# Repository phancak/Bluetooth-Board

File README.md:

# STM32WB55CGU6 Bluetooth Expansion Board  

## Overview  
This project showcases a **high-performance Bluetooth expansion board** based on the **STM32WB55CGU6 module**, a dual-core **Cortex-M4/M0+** MCU with integrated **Bluetooth 5.2** support. Designed for seamless connectivity and modular integration, the board enables **wireless communication** for a wide range of embedded applications.  

This expansion board provides **I2C, USART, and SPI interfaces**, making it a versatile platform for **IoT, industrial control, and smart embedded systems**.  

## Features  
✅ **STM32WB55CGU6 MCU** – Dual-core architecture with BLE 5.2 support  
✅ **Multiple Communication Interfaces** – I2C, USART, SPI for flexible connectivity  
✅ **Ultra-Low Power Operation** – Optimized for battery-powered applications  
✅ **Compact and Modular Design** – Easy integration with host MCUs  
✅ **Secure BLE Communication** – Integrated AES-256 encryption for data protection  

## Applications  
- **IoT & Smart Devices** – Wireless sensors, home automation, asset tracking  
- **Industrial Automation** – Wireless monitoring, factory communication systems  
- **Embedded Development** – Prototyping for BLE-enabled applications  

## Getting Started  
### Hardware Requirements  
- STM32WB55CGU6 Bluetooth Expansion Board  
- Host MCU (STM32, ESP32, Raspberry Pi, etc.)  
- Power Supply (3.3V)  
- USB-to-Serial Debugging Tools  

### Software Requirements  
- **STM32CubeIDE** – Firmware development  
- **STM32CubeWB** – BLE stack and middleware  
- **ST-Link or J-Link** – Debugging and flashing tools  

## Setup & Usage  
1. **Power the Board** – Connect 3.3V power via USB or external source.  
2. **Establish Communication** – Interface using I2C, USART, or SPI.  
3. **Flash Firmware** – Use STM32CubeIDE for code deployment.  
4. **Test Bluetooth Functionality** – Verify BLE communication via a mobile app or BLE-enabled host.  

## Repository Structure  
/Hardware - PCB schematics and design files
/Schematic - Circuit diagrams (PDF, KiCad, Altium, etc.)
/PCB - Board layout files (Gerber, BOM, assembly files)

## Future Enhancements  
- 🔹 **Extended Power Optimization** – Further reducing energy consumption  
- 🔹 **Additional BLE Profiles** – Custom Bluetooth services for enhanced functionality  
- 🔹 **Integration with Cloud Services** – Enable remote monitoring and control  

## License  
This project is open-source under the **MIT License**.  

---

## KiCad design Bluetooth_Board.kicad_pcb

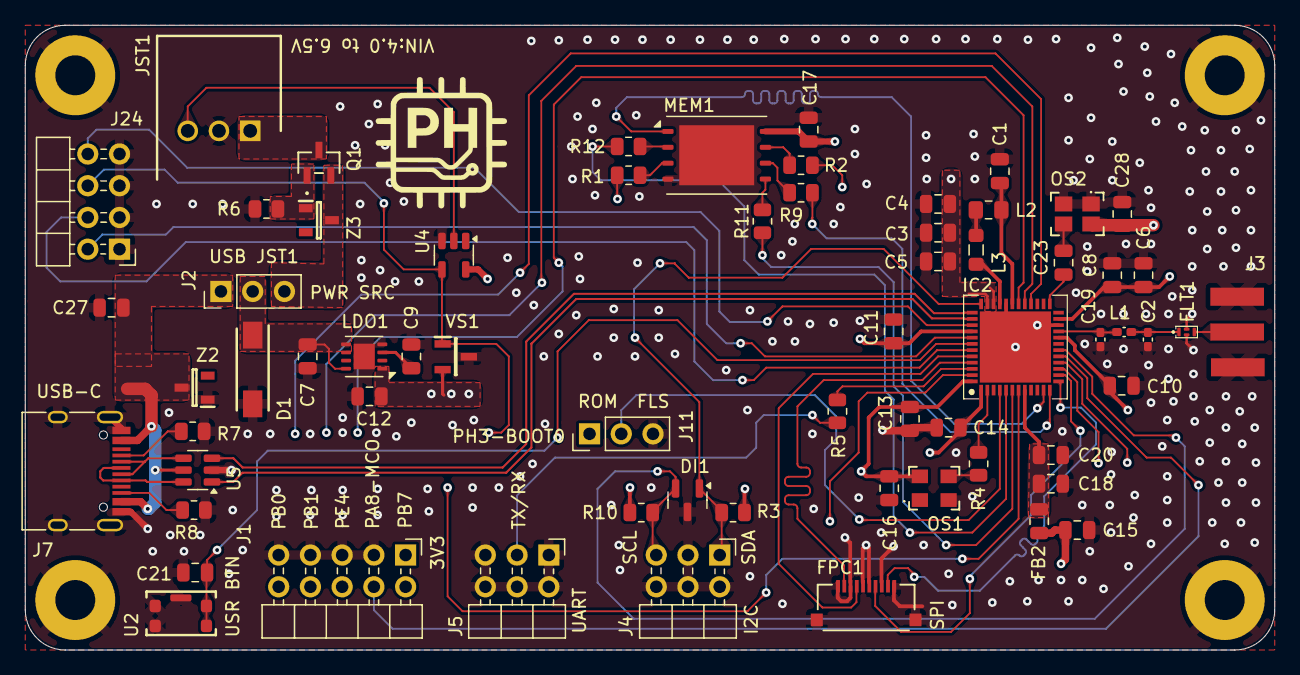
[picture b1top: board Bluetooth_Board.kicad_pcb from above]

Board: 4 copper layers, 100.0 x 50.0 mm, 69 parts (0 on the bottom side), 56 nets.

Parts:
C1, C4, C6, C18, C27: 4u7; C_0805_2012Metric
C2: 0p3 GRM1555C1HR30WA01D; C_0402_1005Metric_Pad0.74x0.62mm_HandSolder
C3, C5, C8, C10, C11, C13, C14, C15, C17, C20, C28: 100n; C_0805_2012Metric
C7: 1u; C_0805_2012Metric
C9, C16: 10n; C_0805_2012Metric
C12: 2u2; C_0805_2012Metric
C19: 0p8 GRM1555C1HR80BA01D; C_0402_1005Metric_Pad0.74x0.62mm_HandSolder
C21: 1uF; C_0805_2012Metric
C23: 1n; C_0805_2012Metric
D1: SMAJ6.0A; DO-214AC-2
DI1: Diode_PESD5V0U2BT-Q; SOT-23
FB2: BLM21AG121BH1D; C_0805_2012Metric
FLT1: DLF162500LT-5028A1
FPC1: FPC_10051922-1010ELF; FPC_10051922_1010
H1, H2, H3, H4: MountingHole_Pad; MountingHole_3.2mm_M3_Pad
IC2: STM32WB55CGU6; STM32WB55CGU6_QFN50P700X700X60-49N-D
J1: I/O_HDR; PinHeader_2x05_P2.54mm_Horizontal
J2: I2S_OR_LJ_OUT; PinHeader_1x03_P2.54mm_Vertical
J3: SMA PCB END LAUNCH JACK ROUND PO; SMA Clip Mount Adapter (top)
J4: I2C1_Headers; PinHeader_2x03_P2.54mm_Horizontal_Court
J5: UART1_HDR; PinHeader_2x03_P2.54mm_Horizontal_Court
J7: USB_C_Receptacle_USB2.0_16P; USB_C_Receptacle_HRO_TYPE-C-31-M-12
J11: BOOT0_Jumper; PinHeader_1x03_P2.54mm_Vertical
J24: SWDB; PinHeader_2x04_P2.54mm_Horizontal
JST1: JST_S3B-XH-2.54; JST_S3B-XH-SHDRRA3W64P0X250_1X3_990X1150X610P
L1: 2n7 LQG15HS2N7S02; L_0402_1005Metric_Pad0.77x0.64mm_HandSolder
L2: 10u Murata LQM21FN100M70L; L_0805_2012Metric_Pad1.15x1.40mm_HandSolder
L3: 10n Murata LQG15WZ10NJ02D; L_0805_2012Metric_Pad1.05x1.20mm_HandSolder
LDO1: LDO_LDLN050PU33R; DFN-8-1EP_3x3mm_P0.65mm_EP1.7x2.05mm
MEM1: MX35LF2G24AD-Z4I; WDFN-8-1EP_8x6mm_P1.27mm_EP6x4.8mm
OS1: Oscillator_ECS-327MVATX-3-CN-TR; Oscillator_ECS327MVATX3CNTR
OS2: Oscillator_ATX-11-F-32.000MHZ-F05-T; Oscillator_ECSTXO32CSMV320ANTR
Q1: MOSFET_SI2333DDS-T1-BE3; MOSFET_ SI2333DDS_SOT_DS-T1-BE3_VIS
R1, R2, R5, R9, R11, R12: 33R; R_0805_2012Metric
R3, R10: 10k; R_0805_2012Metric
R4: 10R; R_0805_2012Metric
R6: 100k; R_0805_2012Metric
R7, R8: 5k1; R_0805_2012Metric
U2: Button_KMR231GLFS
U4: SN74LVC1G07DBVR; SOT-23-5
U5: USBLC6-2SC6; SOT-23-6
VS1: VS_STM1818TWX7F; SOT-23-3_SOT103P237X112-3N
Z2, Z3: Diode_BZX84C6V2-7-F; Diode_BZX84C6V2_SOT96P240X110-3N

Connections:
+3.3V: C3.1, C4.1, C5.1, C6.1, C8.1, C10.1, C11.1, C12.1, C13.1, C14.1, C15.1, C16.2, C17.1, C28.2, FB2.2, IC2.1 (VBAT), IC2.20 (VDD_1), IC2.23 (VDDRF), IC2.34 (VDDSMPS), IC2.35 (VDD_2), IC2.40 (VDDUSB), IC2.48 (VDD_3), J1.1, J11.1, LDO1.1 (OUT), MEM1.8 (VCC), OS1.4 (VDD), OS2.4 (VDD), R3.1, R10.1, U4.5 (VCC), VS1.2 (VCC)
+3.3VA: C18.1, C20.1, FB2.1, IC2.8 (VDDA)
/Interfaces/I2C_SCL_HDR: DI1.2 (K2), IC2.18 (PA9), J4.5, R10.2
/Interfaces/I2C_SDA_HDR: DI1.1 (K1), IC2.36 (PA10), J4.1, R3.2
/Interfaces/I/O_HDR0: IC2.47 (PB7), J1.2
/Interfaces/I/O_HDR1: IC2.17 (PA8), J1.4
/Interfaces/I/O_HDR2: IC2.30 (PE4), J1.6
/Interfaces/I/O_HDR3: IC2.29 (PB1), J1.8
/Interfaces/I/O_HDR4: IC2.28 (PB0), J1.10
/Interfaces/NRST: IC2.7 (NRST), J24.6, U4.4, VS1.1 (~RST)
/Interfaces/SPI_CLK: FPC1.7, IC2.14 (PA5)
/Interfaces/SPI_CS: FPC1.9, IC2.13 (PA4)
/Interfaces/SPI_MISO: FPC1.4, IC2.44 (PB4)
/Interfaces/SPI_MOSI: FPC1.2, IC2.45 (PB5)
/Interfaces/SWCLK: IC2.41 (PA14), J24.2
/Interfaces/SWDIO: IC2.39 (PA13), J24.8
/Interfaces/SWO: IC2.43 (PB3), J24.4
/Interfaces/UART1_TX/RX: IC2.46 (PB6), R5.1
/Interfaces/USR_BTN: C21.2, IC2.42 (PA15), U2.1, U2.2
/Power_Management/MOSFET_PWR: Q1.1 (G), R6.1, Z3.1 (A)
/Power_Management/PWR+: JST1.1 (PWR+), Q1.3 (D)
/Power_Management/PWR+_PP: J2.3, Q1.2 (S), Z3.3 (K)
/Power_Management/RST_PWR: JST1.3 (RST), U4.2
/Power_Management/VIN_LDLN050PU33R: C7.1, D1.1 (K), J2.2, LDO1.5 (EN), LDO1.8 (IN)
/RF, USB/RF1: C19.1, IC2.21 (RF1), L1.1
/RF, USB/RF_ANT: FLT1.3 (OUT), J3.3 (Signal)
/RF, USB/RF_MATCH: C2.1, FLT1.1 (IN), L1.2
/RF, USB/USB_D2+: J7.A6 (D+), J7.B6 (D+), U5.6 (I/O1)
/RF, USB/USB_D2-: J7.A7 (D-), J7.B7 (D-), U5.4 (I/O2)
/RF, USB/USB_DI_D2+: IC2.38 (PA12), U5.1 (I/O1)
/RF, USB/USB_DI_D2-: IC2.37 (PA11), U5.3 (I/O2)
/STM32WB55CGU6/BOOT0: IC2.4 (PH3-BOOT0), J11.2
/STM32WB55CGU6/OSC_IN: C23.1, IC2.25 (OSC_IN)
/STM32WB55CGU6/OSC_OUTPUT: C23.2, OS2.3 (OUTPUT)
/STM32WB55CGU6/PA2_QUADSPI_BK1_NCS: IC2.11 (PA2), MEM1.1 (CS#)
/STM32WB55CGU6/PA3_QUADSPI_CLK: IC2.12 (PA3), R9.1
/STM32WB55CGU6/PA6_QUADSPI_BK1_IO3: IC2.15 (PA6), R2.1
/STM32WB55CGU6/PA7_QUADSPI_BK1_IO2: IC2.16 (PA7), R12.1
/STM32WB55CGU6/PB8_QUADSPI_BK1_IO1: IC2.5 (PB8), R1.2
/STM32WB55CGU6/PB9_QUADSPI_BK1_IO0: IC2.6 (PB9), R11.1
/STM32WB55CGU6/SMPS_FB: C1.1, IC2.31 (VFBSMPS), L2.1
/STM32WB55CGU6/SMPS_LX: IC2.33 (VLXSMPS), L3.2
/STM32WB55CGU6/SMPS_LXL: L2.2, L3.1
GND: C1.2, C2.2, C3.2, C4.2, C5.2, C6.2, C7.2, C8.2, C9.2, C10.2, C11.2, C12.2, C13.2, C14.2, C15.2, C16.1, C17.2, C18.2, C19.2, C20.2, C21.1, C27.2, C28.1, D1.2 (A), DI1.3 (CC), FLT1.2 (GND), FLT1.4 (GND), FPC1.1, FPC1.3, FPC1.5, FPC1.6, FPC1.8, FPC1.10, FPC1.11 (MP1), FPC1.12 (MP2), H1.1, H2.1, H3.1, H4.1, IC2.22 (VSSRF), IC2.32 (VSSSMPS), IC2.49 (GND), J1.3, J1.5, J1.7, J1.9, J3.1 (GND), J3.2 (GND), J4.2, J4.3, J4.4, J4.6, J5.1, J5.2, J5.4, J5.5, J5.6, J7.A1 (GND), J7.A12 (GND), J7.B1 (GND), J7.B12 (GND), J7.S1 (SHIELD), J11.3, J24.1, J24.3, J24.5, J24.7, JST1.2 (PWR-), LDO1.4 (GND_1), LDO1.9 (GND_2), MEM1.4 (GND), MEM1.9 (GND), OS1.2 (GND), OS2.1 (GND_1), OS2.2 (GND_2), R6.2, R7.2, R8.2, U2.3, U2.4, U2.5 (GND), U4.3 (GND), U5.2 (GND), VS1.3 (VSS), Z2.1 (A)
unnamed: IC2.2 (PC14-OSC32_IN), R4.1
unnamed: J5.3, R5.2
unnamed: J7.A5 (CC1), R7.1
unnamed: J7.B5 (CC2), R8.1
unnamed: C9.1, LDO1.3 (FB)
unnamed: MEM1.7 (HOLD#/SIO3), R2.2
unnamed: MEM1.6 (SCLK), R9.2
unnamed: MEM1.5 (SI/SIO0), R11.2
unnamed: MEM1.2 (SO/SIO1), R1.1
unnamed: MEM1.3 (WP#/SIO2), R12.2
unnamed: OS1.3 (OUTPUT), R4.2
VBUS+: C27.1, J2.1, J7.A4 (VBUS), J7.A9 (VBUS), J7.B4 (VBUS), J7.B9 (VBUS), U5.5 (VBUS), Z2.3 (K)

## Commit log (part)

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2025-03-25 Upddate
